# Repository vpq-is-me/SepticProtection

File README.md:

# Overfill protection for Sewage Treatment System

This device used for protection autonomous Sewage Treatment System (STS) ТОПАС-5 (Topas 5) as on picture:

### Topas 5 example

For level overfill measure used 2 float switches: for Incame tank and Drain tank. 
Circuit diagram shown bellow.

### Circuit diagram  

### PCB view  

Controller ESP32 connected to Bluetooth MESH and broadcast state to [home_automation_server](https://github.com/vpq-is-me/home_auto_nodejs.git) (running on Raspberry Pi) and __most importantly__ to [water pump controller](https://github.com/vpq-is-me/WaterPumpController_ESP32.git) to stop water feeding in case of STS failure.

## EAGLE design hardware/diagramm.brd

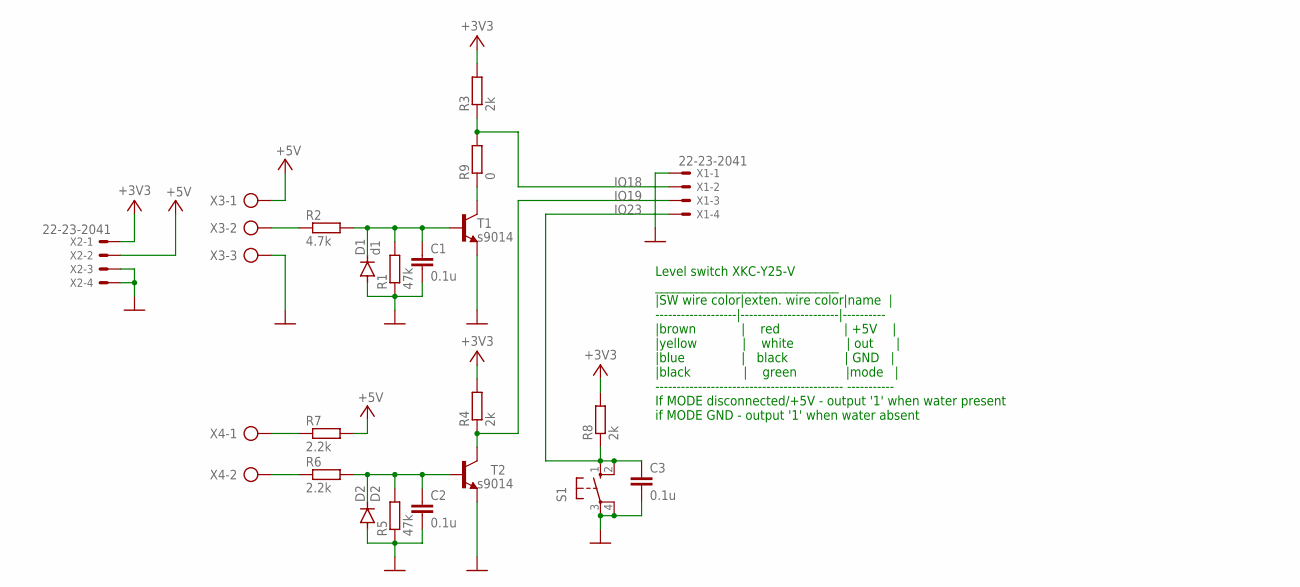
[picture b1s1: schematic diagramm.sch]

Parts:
C1, C2, C3: 0.1u; C1206
D1: d1; DO214AC
D2: D2; DO214AC
R1, R5: 47k; R1206
R2: 4.7k; R1206
R3, R4, R8: 2k; R1206
R6, R7: 2.2k; R1206
R9: 0; R1206
S1: 10-XX; B3F-10XX
T1, T2: s9014; SOT23-BEC
X1, X2: 22-23-2041
X3: AK300/3
X4: AK300/2

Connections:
+3V3: R3.2, R4.2, R8.2, X2.1
+5V: R7.2, X2.2, X3.1
GND: C1.2, C2.2, C3.2, D1.A, D2.A, R1.1, R5.1, S1.3, S1.4 (P1), T1.E, T2.E, X1.1, X2.3, X2.4, X3.3
IO18: R3.1, R9.2, X1.2
IO19: R4.1, T2.C, X1.3
IO23: C3.1, R8.1, S1.1 (S), S1.2 (S1), X1.4
unnamed: R7.1, X4.1
unnamed: R2.1, X3.2
unnamed: C1.1, D1.C, R1.2, R2.2, T1.B
unnamed: R6.1, X4.2
unnamed: R9.1, T1.C
unnamed: C2.1, D2.C, R5.2, R6.2, T2.B

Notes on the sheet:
Level switch XKC-Y25-V _______________________________ |SW wire color|exten. wire color|name | -------------------|-----------------------|---------- |brown | red | +5V | |yellow | white | out | |blue | black | GND | |black | green |mode | -------------------------------------------- ----------- If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

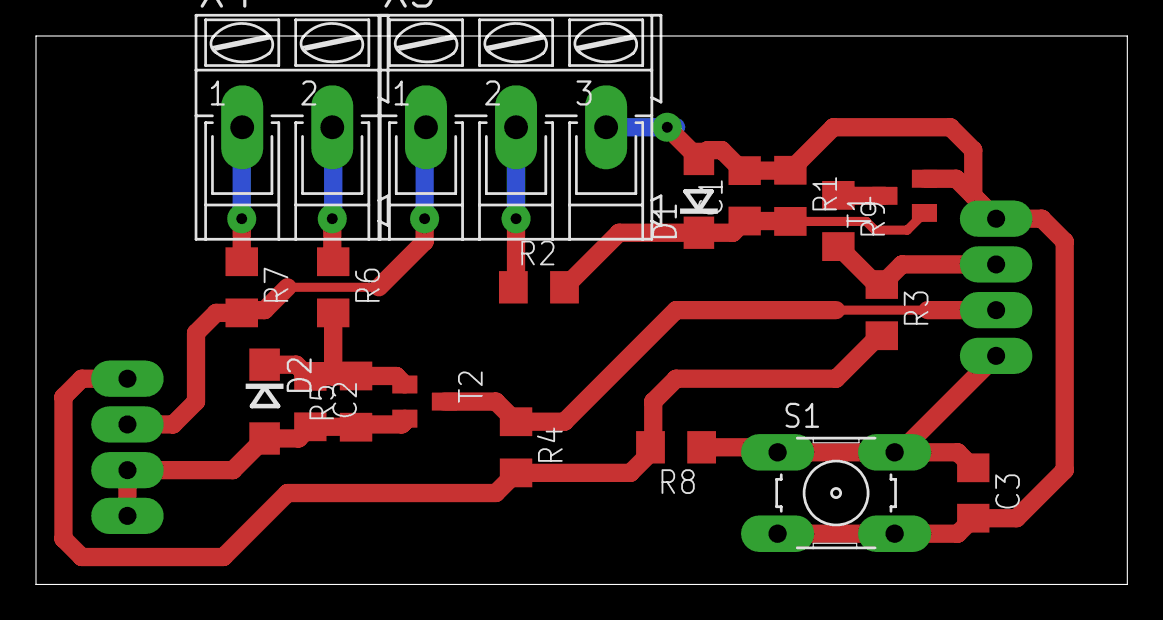
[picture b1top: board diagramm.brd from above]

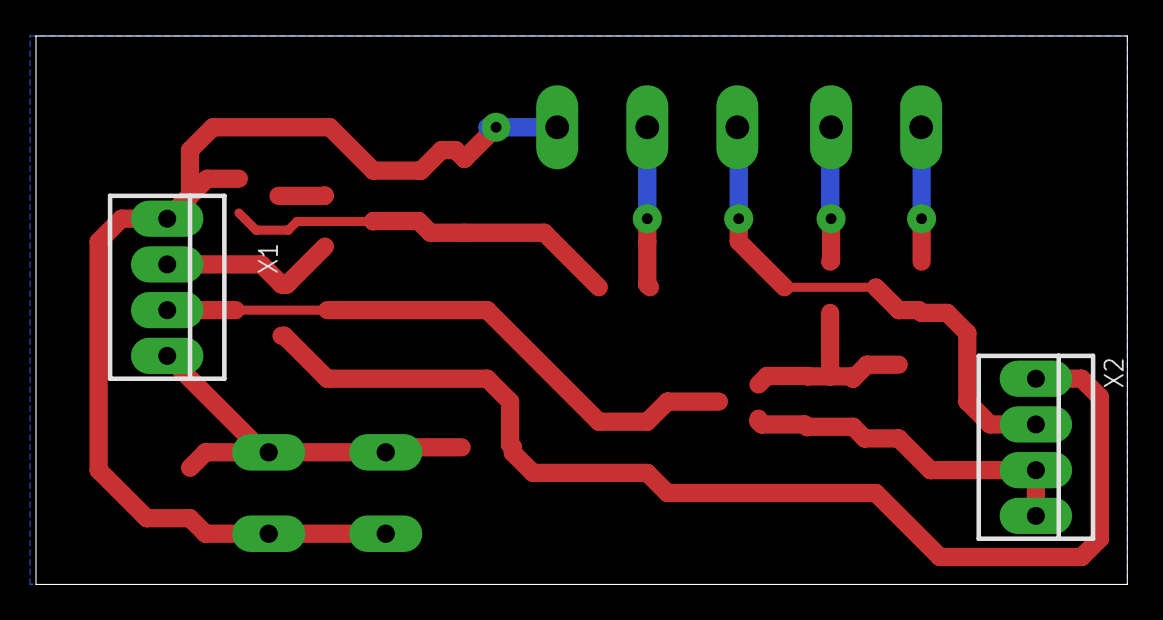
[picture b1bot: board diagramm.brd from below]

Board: 2 copper layers, 60.6 x 30.5 mm, 21 parts (2 on the bottom side), 12 nets.

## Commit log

2023-04-09 V0.1 stable
2023-04-13 moved to other board
2024-04-04 Add description
